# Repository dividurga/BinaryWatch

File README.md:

# Binary Watch Project

Welcome to the Binary Watch project! This repository contains all the files related to the design and development of binary watches using STM32 and ATMega328p microcontrollers. A blog post detailing this can be found at [https://divija.info/](https://divija.info/2024/08/04/binary-display-watch/)

## Project Overview

The Binary Watch is designed to display the time in a "binary but base 10 format". This means each digit of the time in base 10 format is displayed in binary on an LED matrix.

For example, 17:15 is expressed on the LED matrix as:

<pre>
  0   0
  1 0 1
0 1 0 0
1 1 1 1
</pre>

where 1 = LED ON and 0 = LED OFF

## Repository Structure

### watch_STM32
This directory contains the design and firmware for the STM32-based binary watch.

### watch_ATMega328p
This directory contains the design for the ATMega328p-based binary watch.

The firmware from the STM32 version can be modified to work for this hardware. Use the arduino versions of all the libraries and an RTC library for the DS3231 RTC chip

### Setting the Time

- When the code is uploaded for the first time, the RTC time is set to the compile time.
- The current time is displayed on the LED matrix in binary format.
- Everytime you reset or change the battery, the time is set to midnight. This choice is purely aesthetic; I would prefer that my watch always resets to a defined time instead of a random compile time everytime setup() runs. This is achieved by storing a flag in the EEPROM.

## Contributing

Contributions are welcome! I'm still struggling with getting the external oscillator to work with my setup. I think the issue is with my choice of extenal capacitors - they should be 15pF instead of 1pF. The RTC section of the code works perfectly fine on an external Nucleo board, so I think it is a hardware issue. If you have any suggestions or improvements, please open an issue or submit a pull request.

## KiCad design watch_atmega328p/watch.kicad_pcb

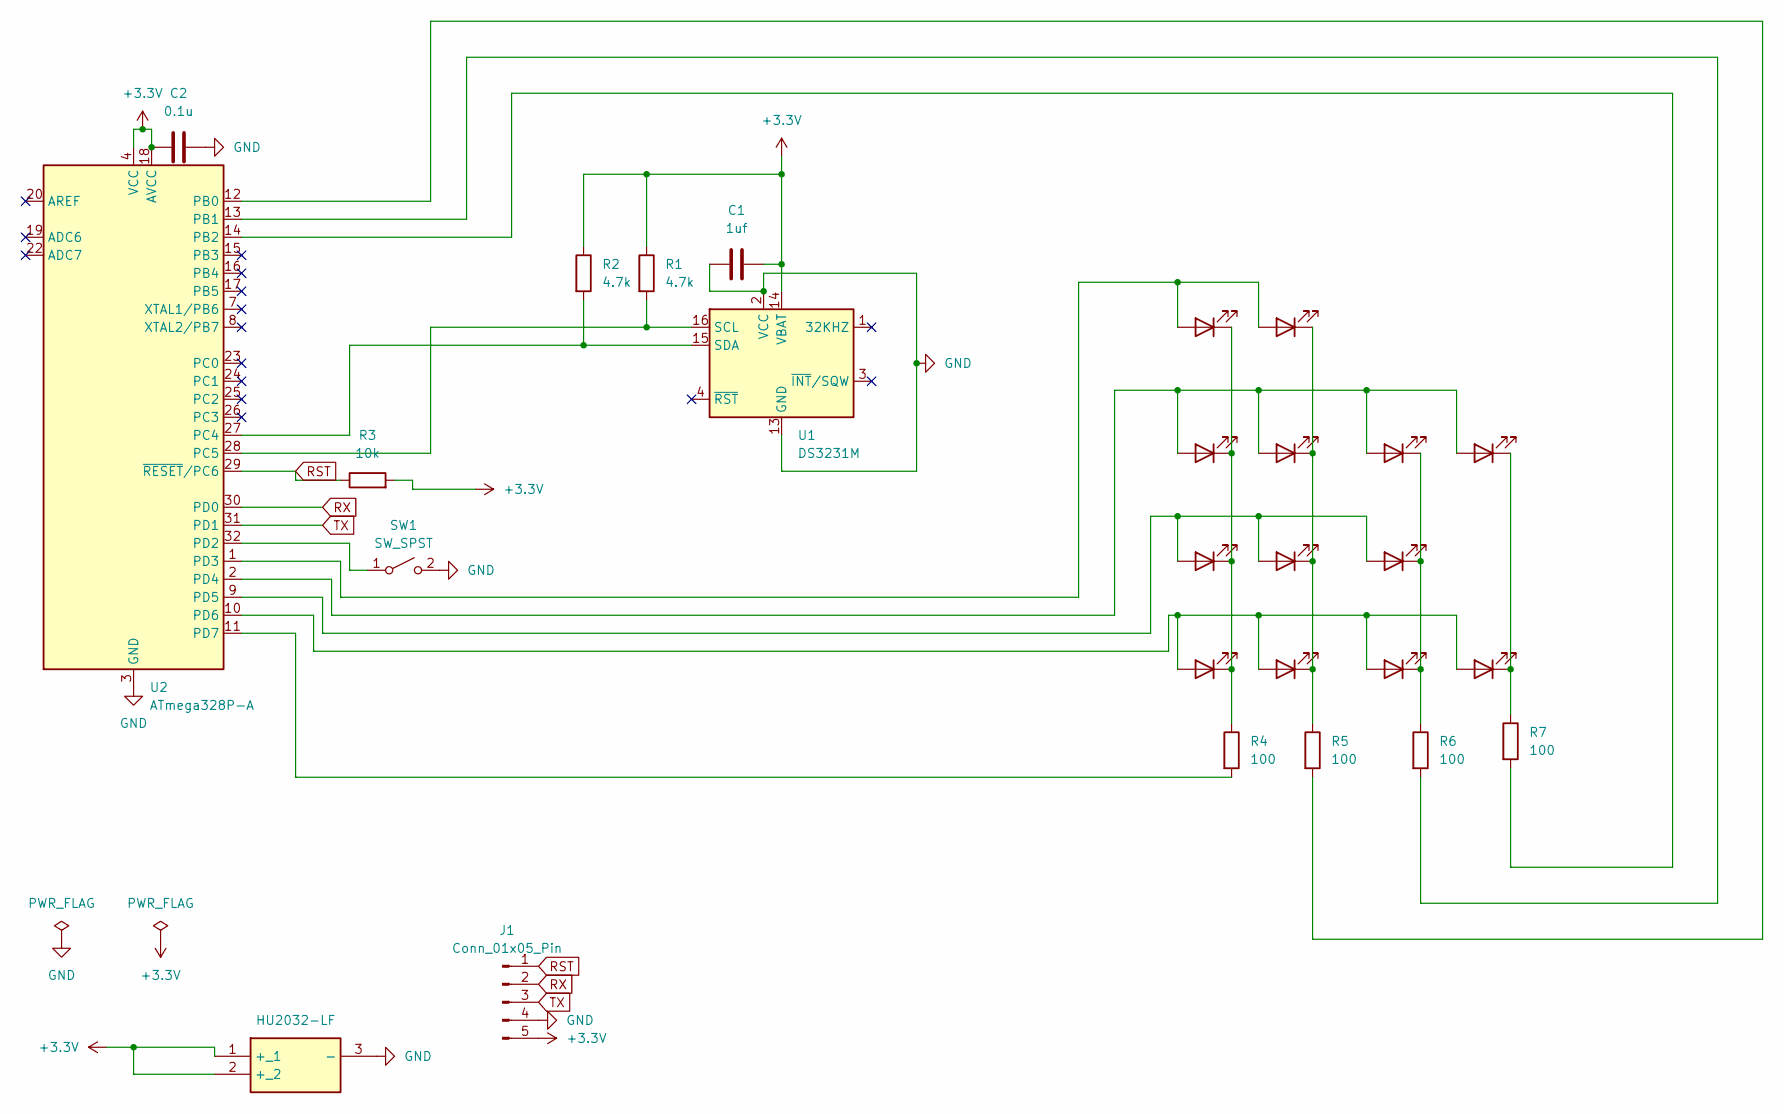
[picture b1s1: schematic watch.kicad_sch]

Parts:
C1: 1uf; C_1206_3216Metric
C2: 0.1u; C_1206_3216Metric
D1, D2, D3, D4, D5, D6, D7, D8, D9, D10, D11, D12, D13: LED; LED_1206_3216Metric
J1: Conn_01x05_Pin; TestPoint_Pad_2.0x2.0mm
R1, R2: 4.7k; R_1206_3216Metric
R3: 10k; R_1206_3216Metric
R4, R5, R6, R7: 100; R_1206_3216Metric
SW1: SW_SPST; SW_TL3342F160QG
U1: DS3231M; SOIC-16W_7.5x10.3mm_P1.27mm
U2: ATmega328P-A; TQFP-32_7x7mm_P0.8mm
U3: HU2032-LF; BAT_BAT-HLD-002-SMT-TR; Mouser Part Number 614-HU2032-LF

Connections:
+3.3V: C1.2, C2.1, J1.5, R1.1, R2.1, R3.2, U1.14 (VBAT), U2.4 (VCC), U2.6 (VCC), U2.18 (AVCC), U3.1 (+_1), U3.2 (+_2)
GND: C1.1, C2.2, J1.4, SW1.2 (B), U1.2 (VCC), U1.5 (GND), U1.6 (GND), U1.7 (GND), U1.8 (GND), U1.9 (GND), U1.10 (GND), U1.11 (GND), U1.12 (GND), U1.13 (GND), U2.3 (GND), U2.5 (GND), U2.21 (GND), U3.3 (-)
unnamed: D1.2 (A), D2.2 (A), U2.1 (PD3)
unnamed: D1.1 (K), D5.1 (K), D8.1 (K), D12.1 (K), R5.1
unnamed: D3.2 (A), D4.2 (A), D5.2 (A), D6.2 (A), U2.2 (PD4)
unnamed: D7.2 (A), D8.2 (A), D9.2 (A), U2.9 (PD5)
unnamed: D10.2 (A), D11.2 (A), D12.2 (A), D13.2 (A), U2.10 (PD6)
unnamed: D3.1 (K), D10.1 (K), R7.1
unnamed: D4.1 (K), D7.1 (K), D11.1 (K), R6.1
unnamed: D2.1 (K), D6.1 (K), D9.1 (K), D13.1 (K), R4.1
unnamed: SW1.1 (A), U2.32 (PD2)
unnamed: R1.2, U1.16 (SCL), U2.28 (PC5)
unnamed: R2.2, U1.15 (SDA), U2.27 (PC4)
unnamed: R5.2, U2.12 (PB0)
unnamed: R6.2, U2.13 (PB1)
unnamed: R7.2, U2.14 (PB2)
unnamed: R4.2, U2.11 (PD7)
RST: J1.1, R3.1, U2.29 (~RESET/PC6)
RX: J1.2, U2.30 (PD0)
TX: J1.3, U2.31 (PD1)

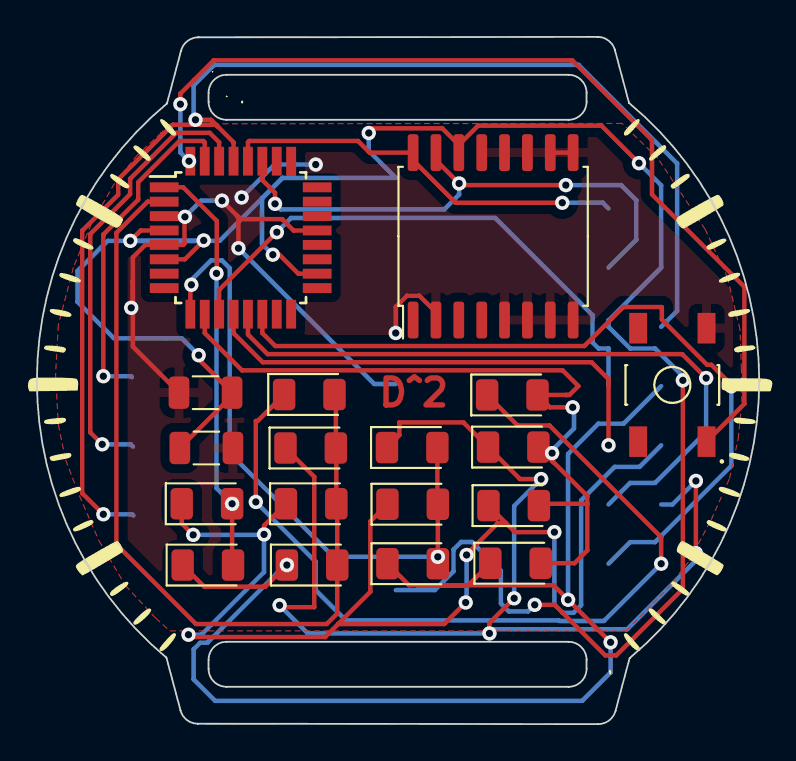
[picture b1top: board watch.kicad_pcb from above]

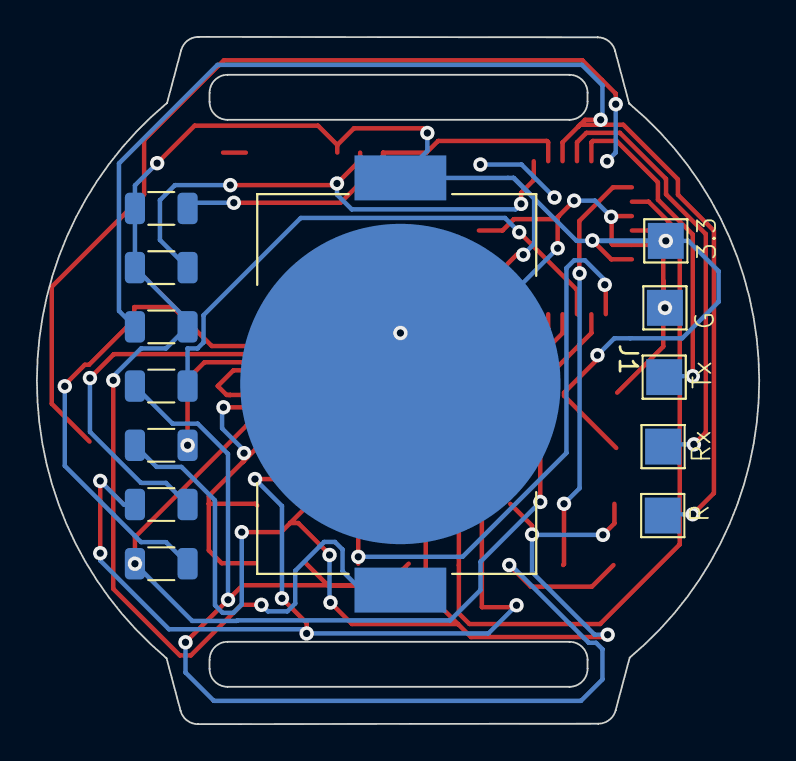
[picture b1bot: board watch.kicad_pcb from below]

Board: 2 copper layers, 40.1 x 38.2 mm, 27 parts (9 on the bottom side), 20 nets.

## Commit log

2024-07-14 Rename watch.kicad_pro to watch_atmega328p/watch.kicad_pro
2024-07-14 added files for atmega version
2024-07-31 Create EEPROMReset
2024-07-31 Added fusion 360 files
